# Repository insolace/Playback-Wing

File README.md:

# Playback-Wing
Concept by Survivor Sound (http://www.survivorsound.com/)

Proof of concept prototype developed by Eric Bateman in 2018

<br>
MIDI DEMO VIDEO (with cat at the end)

<br>
LCD DEMO VIDEO

Playback Wing is a portable MIDI powered lighting controller with LCD, meant for use with GrandMA lighting consoles.  

Features:
* Super thick (3/16") PCB, takes any abuse you can throw at it
* PCB uses a custom switch footprint that can accomodate either CherryMX or 5500 series switches, with or without LEDs. Create your own layout! 
* USB and hardware DIN MIDI
* Optional LCD

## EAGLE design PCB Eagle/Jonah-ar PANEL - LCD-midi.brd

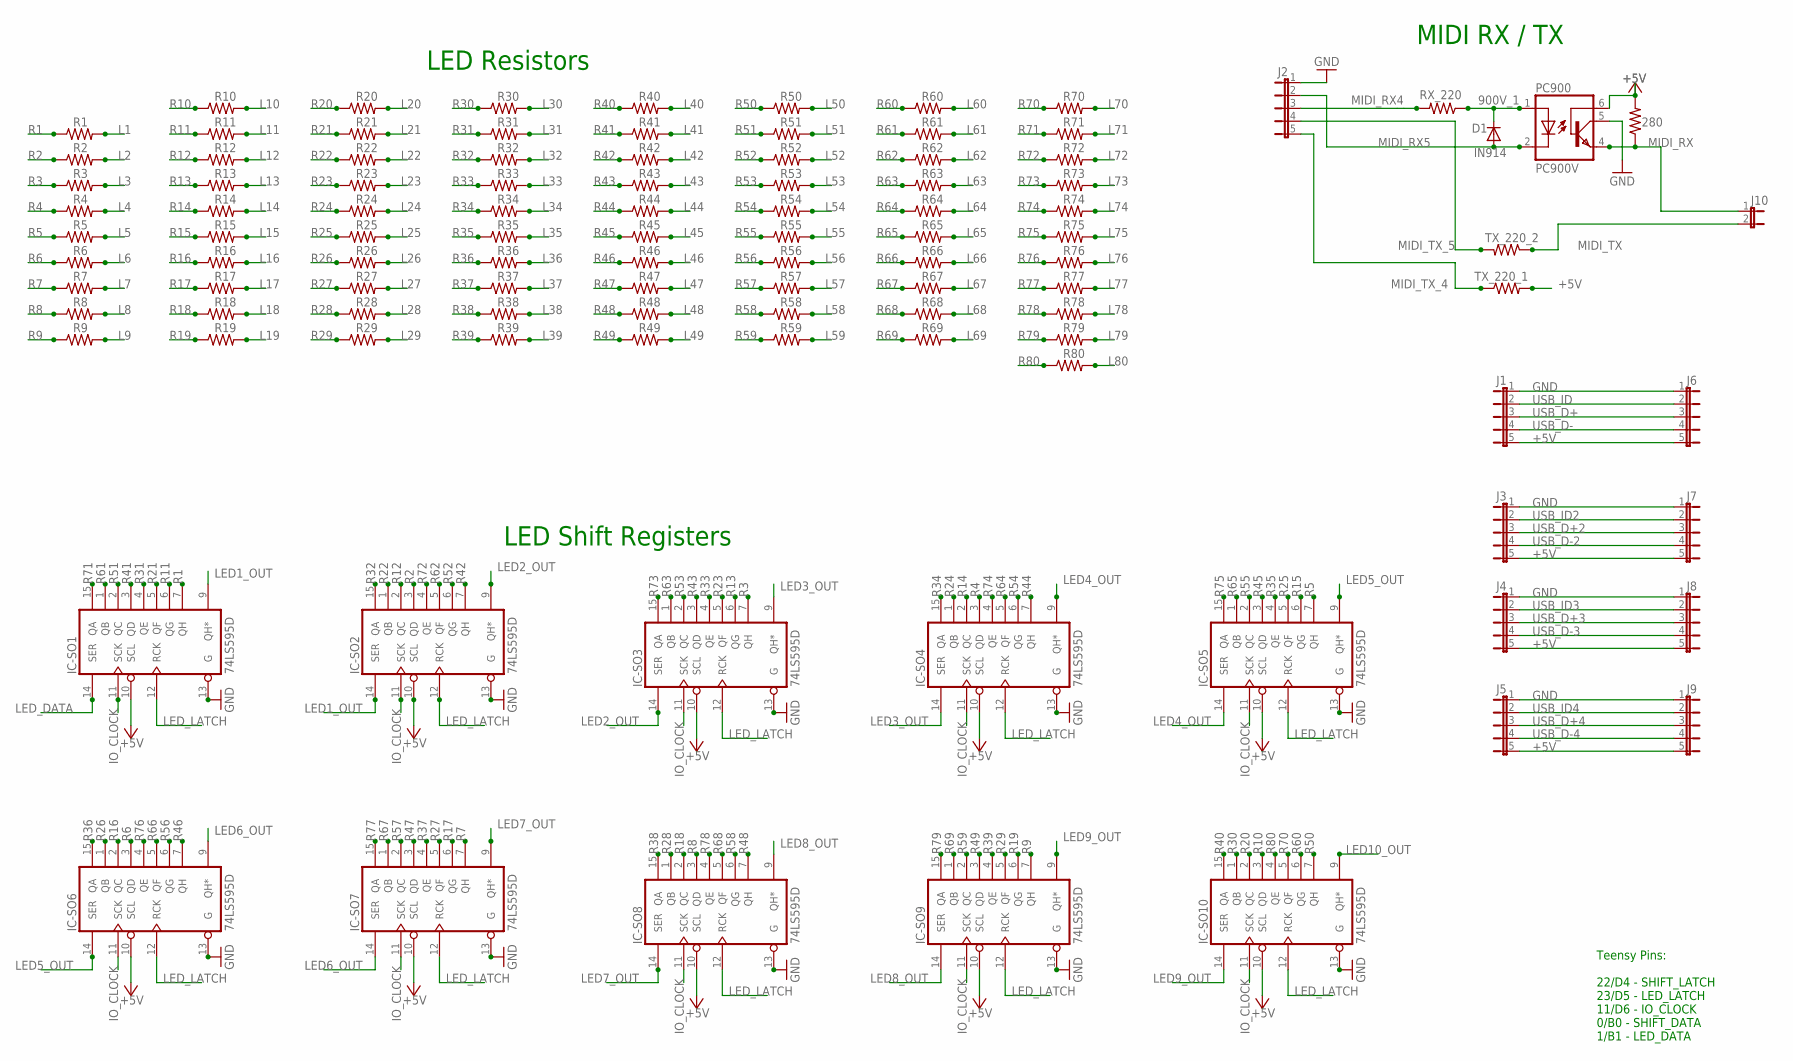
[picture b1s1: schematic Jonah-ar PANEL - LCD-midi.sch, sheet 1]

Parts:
280: 280; 0204/5
D1: IN914; DO34-7
IC-SO1, IC-SO2, IC-SO3, IC-SO4, IC-SO5, IC-SO6, IC-SO7, IC-SO8, IC-SO9, IC-SO10: 74LS595D; SO16
J1, J2, J3, J4, J5, J6, J7, J8, J9: JP5E; JP5
J10: JP1E; JP1
PC900: PC900V; DIL6-SMD
R1, R2, R3, R4, R5, R6, R7, R8, R9, R10, R11, R12, R13, R14, R15, R16, R17, R18, R19, R20, R21, R22, R23, R24, R25, R26, R27, R28, R29, R30, R31, R32, R33, R34, R35, R36, R37, R38, R39, R40, R41, R42, R43, R44, R45, R46, R47, R48, R49, R50, R51, R52, R53, R54, R55, R56, R57, R58, R59, R60, R61, R62, R63, R64, R65, R66, R67, R68, R69, R70, R71, R72, R73, R74, R75, R76, R77, R78, R79, R80: R-US_0204/5; 0204/5
RX_220: 220; 0204/5
TX_220_1, TX_220_2: 220; 0204/5

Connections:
900V_1: D1.C, PC900.1 (A), RX_220.1
+5V: 280.2, IC-SO1.10 (SCL), IC-SO1.16 (+5V), IC-SO2.10 (SCL), IC-SO2.16 (+5V), IC-SO3.10 (SCL), IC-SO3.16 (+5V), IC-SO4.10 (SCL), IC-SO4.16 (+5V), IC-SO5.10 (SCL), IC-SO5.16 (+5V), IC-SO6.10 (SCL), IC-SO6.16 (+5V), IC-SO7.10 (SCL), IC-SO7.16 (+5V), IC-SO8.10 (SCL), IC-SO8.16 (+5V), IC-SO9.10 (SCL), IC-SO9.16 (+5V), IC-SO10.10 (SCL), IC-SO10.16 (+5V), J1.5, J3.5, J4.5, J5.5, J6.5, J7.5, J8.5, J9.5, PC900.6 (BAS), TX_220_1.2; also elsewhere on the board
GND: IC-SO1.8 (GND), IC-SO1.13 (G), IC-SO2.8 (GND), IC-SO2.13 (G), IC-SO3.8 (GND), IC-SO3.13 (G), IC-SO4.8 (GND), IC-SO4.13 (G), IC-SO5.8 (GND), IC-SO5.13 (G), IC-SO6.8 (GND), IC-SO6.13 (G), IC-SO7.8 (GND), IC-SO7.13 (G), IC-SO8.8 (GND), IC-SO8.13 (G), IC-SO9.8 (GND), IC-SO9.13 (G), IC-SO10.8 (GND), IC-SO10.13 (G), J1.1, J2.1, J3.1, J4.1, J5.1, J6.1, J7.1, J8.1, J9.1, PC900.5 (COL); also elsewhere on the board
IO_CLOCK: IC-SO1.11 (SCK), IC-SO2.11 (SCK), IC-SO3.11 (SCK), IC-SO4.11 (SCK), IC-SO5.11 (SCK), IC-SO6.11 (SCK), IC-SO7.11 (SCK), IC-SO8.11 (SCK), IC-SO9.11 (SCK), IC-SO10.11 (SCK); also elsewhere on the board
L1: R1.2; also elsewhere on the board
L2: R2.2; also elsewhere on the board
L3: R3.2; also elsewhere on the board
L4: R4.2; also elsewhere on the board
L5: R5.2; also elsewhere on the board
L6: R6.2; also elsewhere on the board
L7: R7.2; also elsewhere on the board
L8: R8.2; also elsewhere on the board
L9: R9.2; also elsewhere on the board
L10: R10.2; also elsewhere on the board
L11: R11.2; also elsewhere on the board
L12: R12.2; also elsewhere on the board
L13: R13.2; also elsewhere on the board
L14: R14.2; also elsewhere on the board
L15: R15.2; also elsewhere on the board
L16: R16.2; also elsewhere on the board
L17: R17.2; also elsewhere on the board
L18: R18.2; also elsewhere on the board
L19: R19.2; also elsewhere on the board
L20: R20.2; also elsewhere on the board
L21: R21.2; also elsewhere on the board
L22: R22.2; also elsewhere on the board
L23: R23.2; also elsewhere on the board
L24: R24.2; also elsewhere on the board
L25: R25.2; also elsewhere on the board
L26: R26.2; also elsewhere on the board
L27: R27.2; also elsewhere on the board
L28: R28.2; also elsewhere on the board
L29: R29.2; also elsewhere on the board
L30: R30.2; also elsewhere on the board
L31: R31.2; also elsewhere on the board
L32: R32.2; also elsewhere on the board
L33: R33.2; also elsewhere on the board
L34: R34.2; also elsewhere on the board
L35: R35.2; also elsewhere on the board
L36: R36.2; also elsewhere on the board
L37: R37.2; also elsewhere on the board
L38: R38.2; also elsewhere on the board
L39: R39.2; also elsewhere on the board
L40: R40.2; also elsewhere on the board
L41: R41.2; also elsewhere on the board
L42: R42.2; also elsewhere on the board
L43: R43.2; also elsewhere on the board
L44: R44.2; also elsewhere on the board
L45: R45.2; also elsewhere on the board
L46: R46.2; also elsewhere on the board
L47: R47.2; also elsewhere on the board
L48: R48.2; also elsewhere on the board
L49: R49.2; also elsewhere on the board
L50: R50.2; also elsewhere on the board
L51: R51.2; also elsewhere on the board
L52: R52.2; also elsewhere on the board
L53: R53.2; also elsewhere on the board
L54: R54.2; also elsewhere on the board
L55: R55.2; also elsewhere on the board
L56: R56.2; also elsewhere on the board
L57: R57.2; also elsewhere on the board
L58: R58.2; also elsewhere on the board
L59: R59.2; also elsewhere on the board
L60: R60.2; also elsewhere on the board
L61: R61.2; also elsewhere on the board
L62: R62.2; also elsewhere on the board
L63: R63.2; also elsewhere on the board
L64: R64.2; also elsewhere on the board
L65: R65.2; also elsewhere on the board
L66: R66.2; also elsewhere on the board
L67: R67.2; also elsewhere on the board
L68: R68.2; also elsewhere on the board
L69: R69.2; also elsewhere on the board
L70: R70.2; also elsewhere on the board
L71: R71.2; also elsewhere on the board
L72: R72.2; also elsewhere on the board
L73: R73.2; also elsewhere on the board
L74: R74.2; also elsewhere on the board
L75: R75.2; also elsewhere on the board
L76: R76.2; also elsewhere on the board
L77: R77.2; also elsewhere on the board
L78: R78.2; also elsewhere on the board
L79: R79.2; also elsewhere on the board
L80: R80.2; also elsewhere on the board
LED1_OUT: IC-SO1.9 (QH*), IC-SO2.14 (SER)
LED2_OUT: IC-SO2.9 (QH*), IC-SO3.14 (SER)
LED3_OUT: IC-SO3.9 (QH*), IC-SO4.14 (SER)
LED4_OUT: IC-SO4.9 (QH*), IC-SO5.14 (SER)
LED5_OUT: IC-SO5.9 (QH*), IC-SO6.14 (SER)
LED6_OUT: IC-SO6.9 (QH*), IC-SO7.14 (SER)
LED7_OUT: IC-SO7.9 (QH*), IC-SO8.14 (SER)
LED8_OUT: IC-SO8.9 (QH*), IC-SO9.14 (SER)
LED9_OUT: IC-SO9.9 (QH*), IC-SO10.14 (SER)
LED10_OUT: IC-SO10.9 (QH*)
LED_DATA: IC-SO1.14 (SER)
LED_LATCH: IC-SO1.12 (RCK), IC-SO2.12 (RCK), IC-SO3.12 (RCK), IC-SO4.12 (RCK), IC-SO5.12 (RCK), IC-SO6.12 (RCK), IC-SO7.12 (RCK), IC-SO8.12 (RCK), IC-SO9.12 (RCK), IC-SO10.12 (RCK)
MIDI_RX: 280.1, J10.1, PC900.4 (EMI)
MIDI_RX4: J2.3, RX_220.2
MIDI_RX5: D1.A, J2.2, PC900.2 (C)
MIDI_TX: J10.2, TX_220_2.1
MIDI_TX_4: J2.5, TX_220_1.1
MIDI_TX_5: J2.4, TX_220_2.2
R1: IC-SO1.7 (QH), R1.1
R2: IC-SO2.3 (QD), R2.1
R3: IC-SO3.7 (QH), R3.1
R4: IC-SO4.3 (QD), R4.1
R5: IC-SO5.7 (QH), R5.1
R6: IC-SO6.3 (QD), R6.1
R7: IC-SO7.7 (QH), R7.1
R8: IC-SO8.3 (QD), R8.1
R9: IC-SO9.7 (QH), R9.1
R10: IC-SO10.3 (QD), R10.1
R11: IC-SO1.6 (QG), R11.1
R12: IC-SO2.2 (QC), R12.1
R13: IC-SO3.6 (QG), R13.1
R14: IC-SO4.2 (QC), R14.1
R15: IC-SO5.6 (QG), R15.1
R16: IC-SO6.2 (QC), R16.1
R17: IC-SO7.6 (QG), R17.1
R18: IC-SO8.2 (QC), R18.1
R19: IC-SO9.6 (QG), R19.1
R20: IC-SO10.2 (QC), R20.1
R21: IC-SO1.5 (QF), R21.1
R22: IC-SO2.1 (QB), R22.1
R23: IC-SO3.5 (QF), R23.1
R24: IC-SO4.1 (QB), R24.1
R25: IC-SO5.5 (QF), R25.1
R26: IC-SO6.1 (QB), R26.1
R27: IC-SO7.5 (QF), R27.1
R28: IC-SO8.1 (QB), R28.1
R29: IC-SO9.5 (QF), R29.1
R30: IC-SO10.1 (QB), R30.1
R31: IC-SO1.4 (QE), R31.1
R32: IC-SO2.15 (QA), R32.1
R33: IC-SO3.4 (QE), R33.1
R34: IC-SO4.15 (QA), R34.1
R35: IC-SO5.4 (QE), R35.1
R36: IC-SO6.15 (QA), R36.1
R37: IC-SO7.4 (QE), R37.1
R38: IC-SO8.15 (QA), R38.1
R39: IC-SO9.4 (QE), R39.1
R40: IC-SO10.15 (QA), R40.1
R41: IC-SO1.3 (QD), R41.1
R42: IC-SO2.7 (QH), R42.1
R43: IC-SO3.3 (QD), R43.1
R44: IC-SO4.7 (QH), R44.1
R45: IC-SO5.3 (QD), R45.1
R46: IC-SO6.7 (QH), R46.1
R47: IC-SO7.3 (QD), R47.1
R48: IC-SO8.7 (QH), R48.1
R49: IC-SO9.3 (QD), R49.1
R50: IC-SO10.7 (QH), R50.1
R51: IC-SO1.2 (QC), R51.1
R52: IC-SO2.6 (QG), R52.1
R53: IC-SO3.2 (QC), R53.1
R54: IC-SO4.6 (QG), R54.1
R55: IC-SO5.2 (QC), R55.1
R56: IC-SO6.6 (QG), R56.1
R57: IC-SO7.2 (QC), R57.1
R58: IC-SO8.6 (QG), R58.1
R59: IC-SO9.2 (QC), R59.1
R60: IC-SO10.6 (QG), R60.1
R61: IC-SO1.1 (QB), R61.1
R62: IC-SO2.5 (QF), R62.1
R63: IC-SO3.1 (QB), R63.1
R64: IC-SO4.5 (QF), R64.1
R65: IC-SO5.1 (QB), R65.1
R66: IC-SO6.5 (QF), R66.1
R67: IC-SO7.1 (QB), R67.1
R68: IC-SO8.5 (QF), R68.1
R69: IC-SO9.1 (QB), R69.1
R70: IC-SO10.5 (QF), R70.1
R71: IC-SO1.15 (QA), R71.1
R72: IC-SO2.4 (QE), R72.1
R73: IC-SO3.15 (QA), R73.1
R74: IC-SO4.4 (QE), R74.1
R75: IC-SO5.15 (QA), R75.1
R76: IC-SO6.4 (QE), R76.1
R77: IC-SO7.15 (QA), R77.1
R78: IC-SO8.4 (QE), R78.1
R79: IC-SO9.15 (QA), R79.1
R80: IC-SO10.4 (QE), R80.1
USB_D+: J1.3, J6.3
USB_D+2: J3.3, J7.3
USB_D+3: J4.3, J8.3
USB_D+4: J5.3, J9.3
USB_D-: J1.4, J6.4
USB_D-2: J3.4, J7.4
USB_D-3: J4.4, J8.4
USB_D-4: J5.4, J9.4
USB_ID: J1.2, J6.2
USB_ID2: J3.2, J7.2
USB_ID3: J4.2, J8.2
USB_ID4: J5.2, J9.2

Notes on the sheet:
Teensy Pins: 22/D4 - SHIFT_LATCH 23/D5 - LED_LATCH 11/D6 - IO_CLOCK 0/B0 - SHIFT_DATA 1/B1 - LED_DATA
MIDI RX / TX
LED Resistors
LED Shift Registers

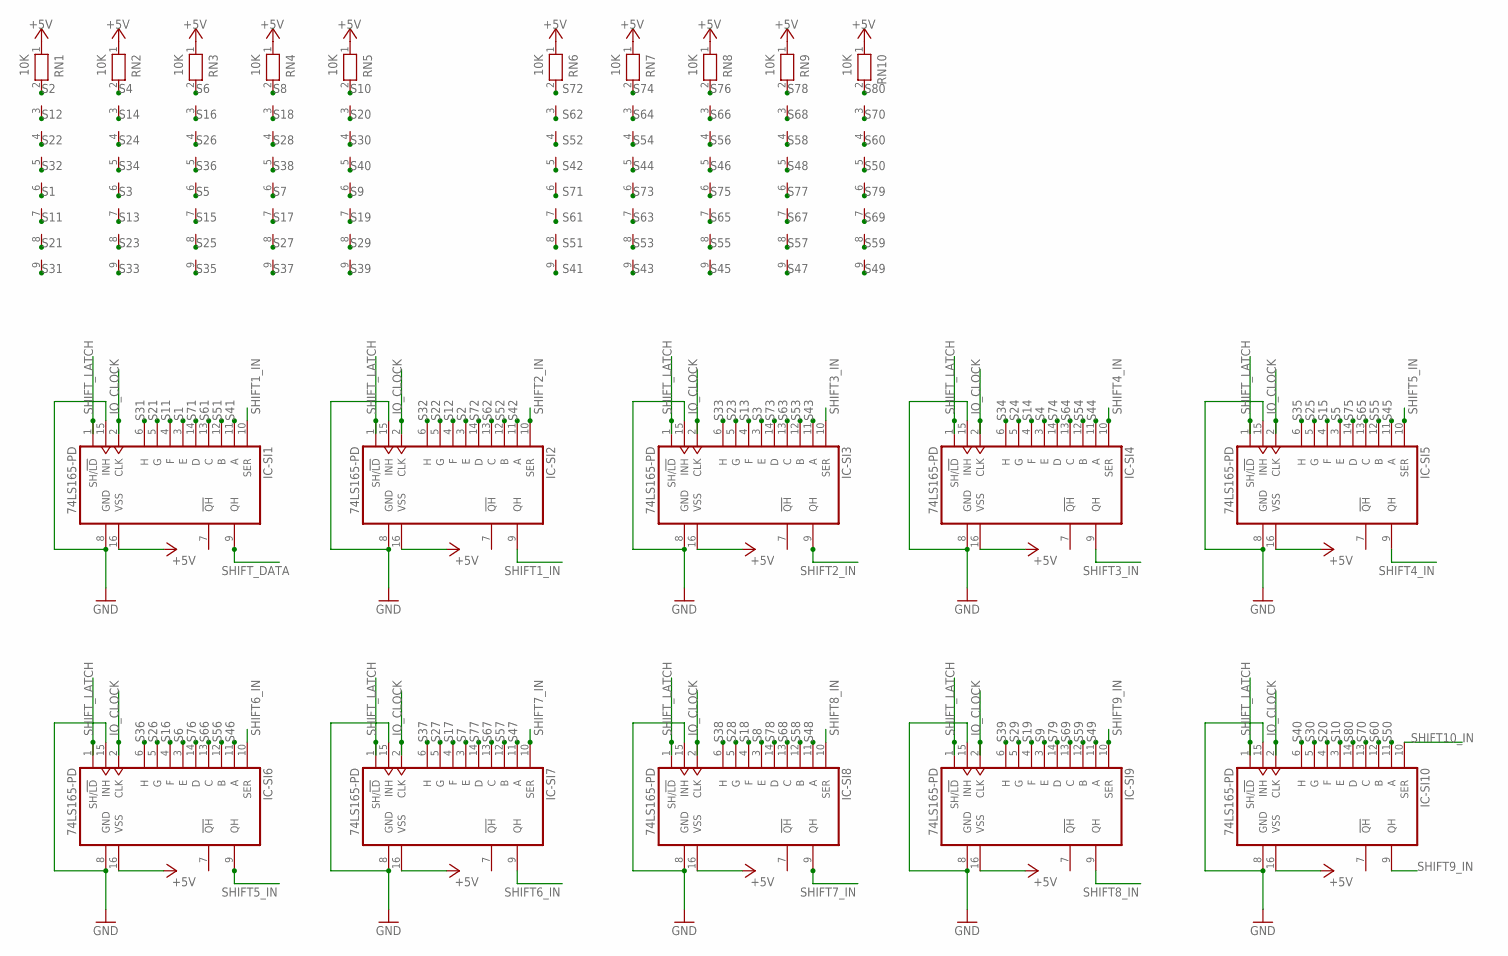
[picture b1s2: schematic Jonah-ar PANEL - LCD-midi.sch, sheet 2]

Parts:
IC-SI1, IC-SI2, IC-SI3, IC-SI4, IC-SI5, IC-SI6, IC-SI7, IC-SI8, IC-SI9, IC-SI10: 74LS165-PD; SO16
RN1, RN2, RN3, RN4, RN5, RN6, RN7, RN8, RN9, RN10: 10K; RN-9

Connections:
+5V: IC-SI1.16 (VSS), IC-SI2.16 (VSS), IC-SI3.16 (VSS), IC-SI4.16 (VSS), IC-SI5.16 (VSS), IC-SI6.16 (VSS), IC-SI7.16 (VSS), IC-SI8.16 (VSS), IC-SI9.16 (VSS), IC-SI10.16 (VSS), RN1.1, RN2.1, RN3.1, RN4.1, RN5.1, RN6.1, RN7.1, RN8.1, RN9.1, RN10.1; also elsewhere on the board
GND: IC-SI1.8 (GND), IC-SI1.15 (INH), IC-SI2.8 (GND), IC-SI2.15 (INH), IC-SI3.8 (GND), IC-SI3.15 (INH), IC-SI4.8 (GND), IC-SI4.15 (INH), IC-SI5.8 (GND), IC-SI5.15 (INH), IC-SI6.8 (GND), IC-SI6.15 (INH), IC-SI7.8 (GND), IC-SI7.15 (INH), IC-SI8.8 (GND), IC-SI8.15 (INH), IC-SI9.8 (GND), IC-SI9.15 (INH), IC-SI10.8 (GND), IC-SI10.15 (INH); also elsewhere on the board
IO_CLOCK: IC-SI1.2 (CLK), IC-SI2.2 (CLK), IC-SI3.2 (CLK), IC-SI4.2 (CLK), IC-SI5.2 (CLK), IC-SI6.2 (CLK), IC-SI7.2 (CLK), IC-SI8.2 (CLK), IC-SI9.2 (CLK), IC-SI10.2 (CLK); also elsewhere on the board
S1: IC-SI1.3 (E), RN1.6; also elsewhere on the board
S2: IC-SI2.3 (E), RN1.2; also elsewhere on the board
S3: IC-SI3.3 (E), RN2.6; also elsewhere on the board
S4: IC-SI4.3 (E), RN2.2; also elsewhere on the board
S5: IC-SI5.3 (E), RN3.6; also elsewhere on the board
S6: IC-SI6.3 (E), RN3.2; also elsewhere on the board
S7: IC-SI7.3 (E), RN4.6; also elsewhere on the board
S8: IC-SI8.3 (E), RN4.2; also elsewhere on the board
S9: IC-SI9.3 (E), RN5.6; also elsewhere on the board
S10: IC-SI10.3 (E), RN5.2; also elsewhere on the board
S11: IC-SI1.4 (F), RN1.7; also elsewhere on the board
S12: IC-SI2.4 (F), RN1.3; also elsewhere on the board
S13: IC-SI3.4 (F), RN2.7; also elsewhere on the board
S14: IC-SI4.4 (F), RN2.3; also elsewhere on the board
S15: IC-SI5.4 (F), RN3.7; also elsewhere on the board
S16: IC-SI6.4 (F), RN3.3; also elsewhere on the board
S17: IC-SI7.4 (F), RN4.7; also elsewhere on the board
S18: IC-SI8.4 (F), RN4.3; also elsewhere on the board
S19: IC-SI9.4 (F), RN5.7; also elsewhere on the board
S20: IC-SI10.4 (F), RN5.3; also elsewhere on the board
S21: IC-SI1.5 (G), RN1.8; also elsewhere on the board
S22: IC-SI2.5 (G), RN1.4; also elsewhere on the board
S23: IC-SI3.5 (G), RN2.8; also elsewhere on the board
S24: IC-SI4.5 (G), RN2.4; also elsewhere on the board
S25: IC-SI5.5 (G), RN3.8; also elsewhere on the board
S26: IC-SI6.5 (G), RN3.4; also elsewhere on the board
S27: IC-SI7.5 (G), RN4.8; also elsewhere on the board
S28: IC-SI8.5 (G), RN4.4; also elsewhere on the board
S29: IC-SI9.5 (G), RN5.8; also elsewhere on the board
S30: IC-SI10.5 (G), RN5.4; also elsewhere on the board
S31: IC-SI1.6 (H), RN1.9; also elsewhere on the board
S32: IC-SI2.6 (H), RN1.5; also elsewhere on the board
S33: IC-SI3.6 (H), RN2.9; also elsewhere on the board
S34: IC-SI4.6 (H), RN2.5; also elsewhere on the board
S35: IC-SI5.6 (H), RN3.9; also elsewhere on the board
S36: IC-SI6.6 (H), RN3.5; also elsewhere on the board
S37: IC-SI7.6 (H), RN4.9; also elsewhere on the board
S38: IC-SI8.6 (H), RN4.5; also elsewhere on the board
S39: IC-SI9.6 (H), RN5.9; also elsewhere on the board
S40: IC-SI10.6 (H), RN5.5; also elsewhere on the board
S41: IC-SI1.11 (A), RN6.9; also elsewhere on the board
S42: IC-SI2.11 (A), RN6.5; also elsewhere on the board
S43: IC-SI3.11 (A), RN7.9; also elsewhere on the board
S44: IC-SI4.11 (A), RN7.5; also elsewhere on the board
S45: IC-SI5.11 (A), RN8.9; also elsewhere on the board
S46: IC-SI6.11 (A), RN8.5; also elsewhere on the board
S47: IC-SI7.11 (A), RN9.9; also elsewhere on the board
S48: IC-SI8.11 (A), RN9.5; also elsewhere on the board
S49: IC-SI9.11 (A), RN10.9; also elsewhere on the board
S50: IC-SI10.11 (A), RN10.5; also elsewhere on the board
S51: IC-SI1.12 (B), RN6.8; also elsewhere on the board
S52: IC-SI2.12 (B), RN6.4; also elsewhere on the board
S53: IC-SI3.12 (B), RN7.8; also elsewhere on the board
S54: IC-SI4.12 (B), RN7.4; also elsewhere on the board
S55: IC-SI5.12 (B), RN8.8; also elsewhere on the board
S56: IC-SI6.12 (B), RN8.4; also elsewhere on the board
S57: IC-SI7.12 (B), RN9.8; also elsewhere on the board
S58: IC-SI8.12 (B), RN9.4; also elsewhere on the board
S59: IC-SI9.12 (B), RN10.8; also elsewhere on the board
S60: IC-SI10.12 (B), RN10.4; also elsewhere on the board
S61: IC-SI1.13 (C), RN6.7; also elsewhere on the board
S62: IC-SI2.13 (C), RN6.3; also elsewhere on the board
S63: IC-SI3.13 (C), RN7.7; also elsewhere on the board
S64: IC-SI4.13 (C), RN7.3; also elsewhere on the board
S65: IC-SI5.13 (C), RN8.7; also elsewhere on the board
S66: IC-SI6.13 (C), RN8.3; also elsewhere on the board
S67: IC-SI7.13 (C), RN9.7; also elsewhere on the board
S68: IC-SI8.13 (C), RN9.3; also elsewhere on the board
S69: IC-SI9.13 (C), RN10.7; also elsewhere on the board
S70: IC-SI10.13 (C), RN10.3; also elsewhere on the board
S71: IC-SI1.14 (D), RN6.6; also elsewhere on the board
S72: IC-SI2.14 (D), RN6.2; also elsewhere on the board
S73: IC-SI3.14 (D), RN7.6; also elsewhere on the board
S74: IC-SI4.14 (D), RN7.2; also elsewhere on the board
S75: IC-SI5.14 (D), RN8.6; also elsewhere on the board
S76: IC-SI6.14 (D), RN8.2; also elsewhere on the board
S77: IC-SI7.14 (D), RN9.6; also elsewhere on the board
S78: IC-SI8.14 (D), RN9.2; also elsewhere on the board
S79: IC-SI9.14 (D), RN10.6; also elsewhere on the board
S80: IC-SI10.14 (D), RN10.2; also elsewhere on the board
SHIFT1_IN: IC-SI1.10 (SER), IC-SI2.9 (QH)
SHIFT2_IN: IC-SI2.10 (SER), IC-SI3.9 (QH)
SHIFT3_IN: IC-SI3.10 (SER), IC-SI4.9 (QH)
SHIFT4_IN: IC-SI4.10 (SER), IC-SI5.9 (QH)
SHIFT5_IN: IC-SI5.10 (SER), IC-SI6.9 (QH)
SHIFT6_IN: IC-SI6.10 (SER), IC-SI7.9 (QH)
SHIFT7_IN: IC-SI7.10 (SER), IC-SI8.9 (QH)
SHIFT8_IN: IC-SI8.10 (SER), IC-SI9.9 (QH)
SHIFT9_IN: IC-SI9.10 (SER), IC-SI10.9 (QH)
SHIFT10_IN: IC-SI10.10 (SER)
SHIFT_DATA: IC-SI1.9 (QH)
SHIFT_LATCH: IC-SI1.1 (SH/!LD), IC-SI2.1 (SH/!LD), IC-SI3.1 (SH/!LD), IC-SI4.1 (SH/!LD), IC-SI5.1 (SH/!LD), IC-SI6.1 (SH/!LD), IC-SI7.1 (SH/!LD), IC-SI8.1 (SH/!LD), IC-SI9.1 (SH/!LD), IC-SI10.1 (SH/!LD)

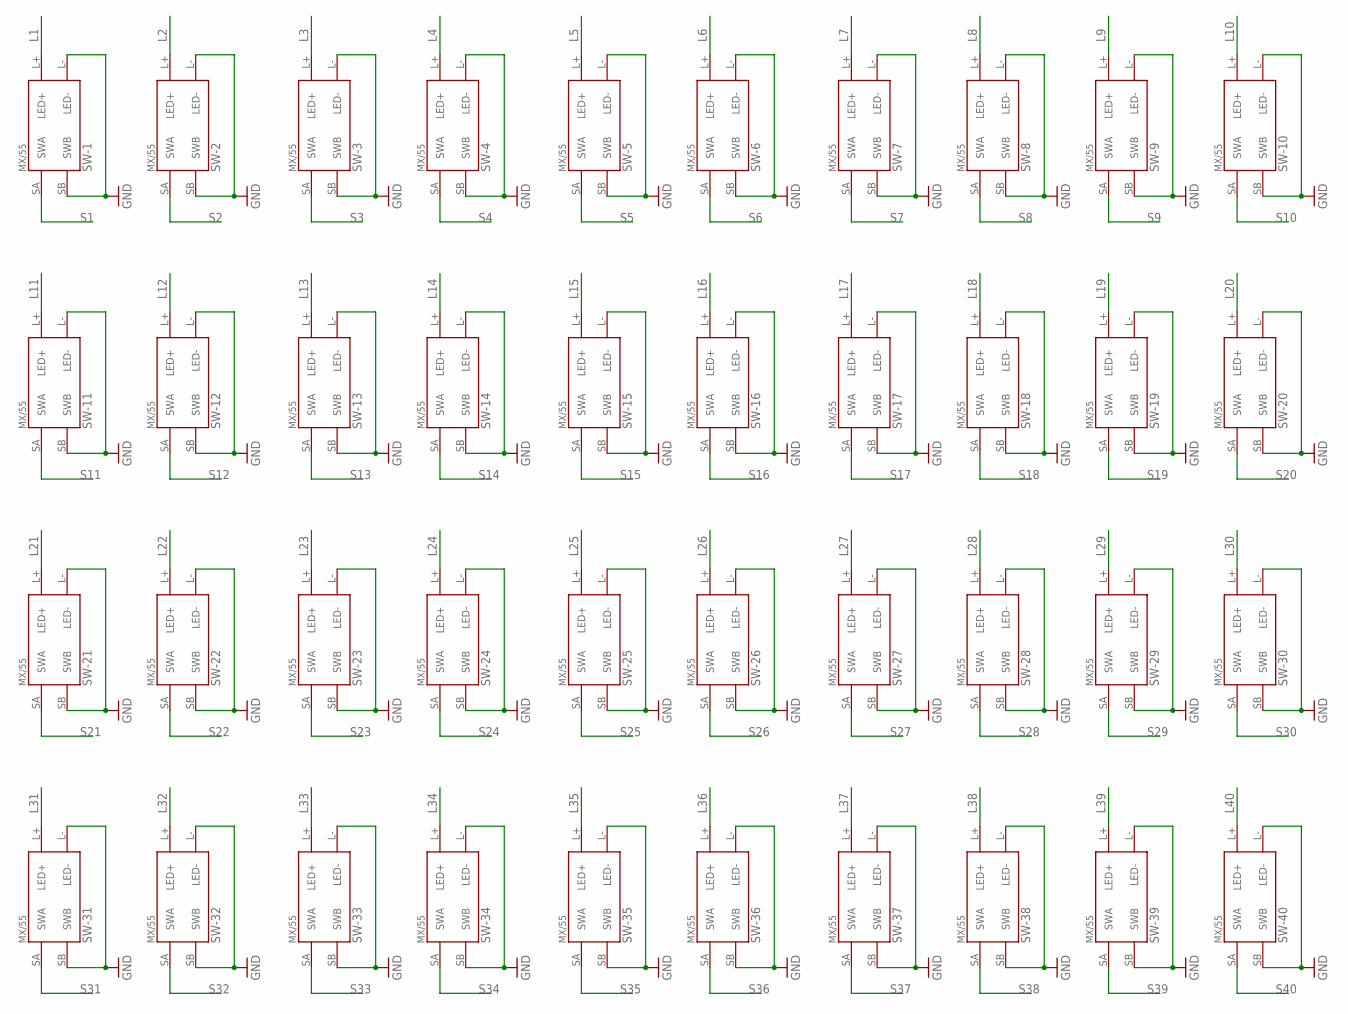
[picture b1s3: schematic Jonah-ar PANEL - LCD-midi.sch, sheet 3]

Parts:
SW-1, SW-2, SW-3, SW-4, SW-5, SW-6, SW-7, SW-8, SW-9, SW-10, SW-11, SW-12, SW-13, SW-14, SW-15, SW-16, SW-17, SW-18, SW-19, SW-20, SW-21, SW-22, SW-23, SW-24, SW-25, SW-26, SW-27, SW-28, SW-29, SW-30, SW-31, SW-32, SW-33, SW-34, SW-35, SW-36, SW-37, SW-38, SW-39, SW-40: CHERRY-MX-LED

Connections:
GND: SW-1.L- (LED-), SW-1.SB (SWB), SW-2.L- (LED-), SW-2.SB (SWB), SW-3.L- (LED-), SW-3.SB (SWB), SW-4.L- (LED-), SW-4.SB (SWB), SW-5.L- (LED-), SW-5.SB (SWB), SW-6.L- (LED-), SW-6.SB (SWB), SW-7.L- (LED-), SW-7.SB (SWB), SW-8.L- (LED-), SW-8.SB (SWB), SW-9.L- (LED-), SW-9.SB (SWB), SW-10.L- (LED-), SW-10.SB (SWB), SW-11.L- (LED-), SW-11.SB (SWB), SW-12.L- (LED-), SW-12.SB (SWB), SW-13.L- (LED-), SW-13.SB (SWB), SW-14.L- (LED-), SW-14.SB (SWB), SW-15.L- (LED-), SW-15.SB (SWB), SW-16.L- (LED-), SW-16.SB (SWB), SW-17.L- (LED-), SW-17.SB (SWB), SW-18.L- (LED-), SW-18.SB (SWB), SW-19.L- (LED-), SW-19.SB (SWB), SW-20.L- (LED-), SW-20.SB (SWB), SW-21.L- (LED-), SW-21.SB (SWB), SW-22.L- (LED-), SW-22.SB (SWB), SW-23.L- (LED-), SW-23.SB (SWB), SW-24.L- (LED-), SW-24.SB (SWB), SW-25.L- (LED-), SW-25.SB (SWB), SW-26.L- (LED-), SW-26.SB (SWB), SW-27.L- (LED-), SW-27.SB (SWB), SW-28.L- (LED-), SW-28.SB (SWB), SW-29.L- (LED-), SW-29.SB (SWB), SW-30.L- (LED-), SW-30.SB (SWB), SW-31.L- (LED-), SW-31.SB (SWB), SW-32.L- (LED-), SW-32.SB (SWB), SW-33.L- (LED-), SW-33.SB (SWB), SW-34.L- (LED-), SW-34.SB (SWB), SW-35.L- (LED-), SW-35.SB (SWB), SW-36.L- (LED-), SW-36.SB (SWB), SW-37.L- (LED-), SW-37.SB (SWB), SW-38.L- (LED-), SW-38.SB (SWB), SW-39.L- (LED-), SW-39.SB (SWB), SW-40.L- (LED-), SW-40.SB (SWB); also elsewhere on the board
L1: SW-1.L+ (LED+); also elsewhere on the board
L2: SW-2.L+ (LED+); also elsewhere on the board
L3: SW-3.L+ (LED+); also elsewhere on the board
L4: SW-4.L+ (LED+); also elsewhere on the board
L5: SW-5.L+ (LED+); also elsewhere on the board
L6: SW-6.L+ (LED+); also elsewhere on the board
L7: SW-7.L+ (LED+); also elsewhere on the board
L8: SW-8.L+ (LED+); also elsewhere on the board
L9: SW-9.L+ (LED+); also elsewhere on the board
L10: SW-10.L+ (LED+); also elsewhere on the board
L11: SW-11.L+ (LED+); also elsewhere on the board
L12: SW-12.L+ (LED+); also elsewhere on the board
L13: SW-13.L+ (LED+); also elsewhere on the board
L14: SW-14.L+ (LED+); also elsewhere on the board
L15: SW-15.L+ (LED+); also elsewhere on the board
L16: SW-16.L+ (LED+); also elsewhere on the board
L17: SW-17.L+ (LED+); also elsewhere on the board
L18: SW-18.L+ (LED+); also elsewhere on the board
L19: SW-19.L+ (LED+); also elsewhere on the board
L20: SW-20.L+ (LED+); also elsewhere on the board
L21: SW-21.L+ (LED+); also elsewhere on the board
L22: SW-22.L+ (LED+); also elsewhere on the board
L23: SW-23.L+ (LED+); also elsewhere on the board
L24: SW-24.L+ (LED+); also elsewhere on the board
L25: SW-25.L+ (LED+); also elsewhere on the board
L26: SW-26.L+ (LED+); also elsewhere on the board
L27: SW-27.L+ (LED+); also elsewhere on the board
L28: SW-28.L+ (LED+); also elsewhere on the board
L29: SW-29.L+ (LED+); also elsewhere on the board
L30: SW-30.L+ (LED+); also elsewhere on the board
L31: SW-31.L+ (LED+); also elsewhere on the board
L32: SW-32.L+ (LED+); also elsewhere on the board
L33: SW-33.L+ (LED+); also elsewhere on the board
L34: SW-34.L+ (LED+); also elsewhere on the board
L35: SW-35.L+ (LED+); also elsewhere on the board
L36: SW-36.L+ (LED+); also elsewhere on the board
L37: SW-37.L+ (LED+); also elsewhere on the board
L38: SW-38.L+ (LED+); also elsewhere on the board
L39: SW-39.L+ (LED+); also elsewhere on the board
L40: SW-40.L+ (LED+); also elsewhere on the board
S1: SW-1.SA (SWA); also elsewhere on the board
S2: SW-2.SA (SWA); also elsewhere on the board
S3: SW-3.SA (SWA); also elsewhere on the board
S4: SW-4.SA (SWA); also elsewhere on the board
S5: SW-5.SA (SWA); also elsewhere on the board
S6: SW-6.SA (SWA); also elsewhere on the board
S7: SW-7.SA (SWA); also elsewhere on the board
S8: SW-8.SA (SWA); also elsewhere on the board
S9: SW-9.SA (SWA); also elsewhere on the board
S10: SW-10.SA (SWA); also elsewhere on the board
S11: SW-11.SA (SWA); also elsewhere on the board
S12: SW-12.SA (SWA); also elsewhere on the board
S13: SW-13.SA (SWA); also elsewhere on the board
S14: SW-14.SA (SWA); also elsewhere on the board
S15: SW-15.SA (SWA); also elsewhere on the board
S16: SW-16.SA (SWA); also elsewhere on the board
S17: SW-17.SA (SWA); also elsewhere on the board
S18: SW-18.SA (SWA); also elsewhere on the board
S19: SW-19.SA (SWA); also elsewhere on the board
S20: SW-20.SA (SWA); also elsewhere on the board
S21: SW-21.SA (SWA); also elsewhere on the board
S22: SW-22.SA (SWA); also elsewhere on the board
S23: SW-23.SA (SWA); also elsewhere on the board
S24: SW-24.SA (SWA); also elsewhere on the board
S25: SW-25.SA (SWA); also elsewhere on the board
S26: SW-26.SA (SWA); also elsewhere on the board
S27: SW-27.SA (SWA); also elsewhere on the board
S28: SW-28.SA (SWA); also elsewhere on the board
S29: SW-29.SA (SWA); also elsewhere on the board
S30: SW-30.SA (SWA); also elsewhere on the board
S31: SW-31.SA (SWA); also elsewhere on the board
S32: SW-32.SA (SWA); also elsewhere on the board
S33: SW-33.SA (SWA); also elsewhere on the board
S34: SW-34.SA (SWA); also elsewhere on the board
S35: SW-35.SA (SWA); also elsewhere on the board
S36: SW-36.SA (SWA); also elsewhere on the board
S37: SW-37.SA (SWA); also elsewhere on the board
S38: SW-38.SA (SWA); also elsewhere on the board
S39: SW-39.SA (SWA); also elsewhere on the board
S40: SW-40.SA (SWA); also elsewhere on the board

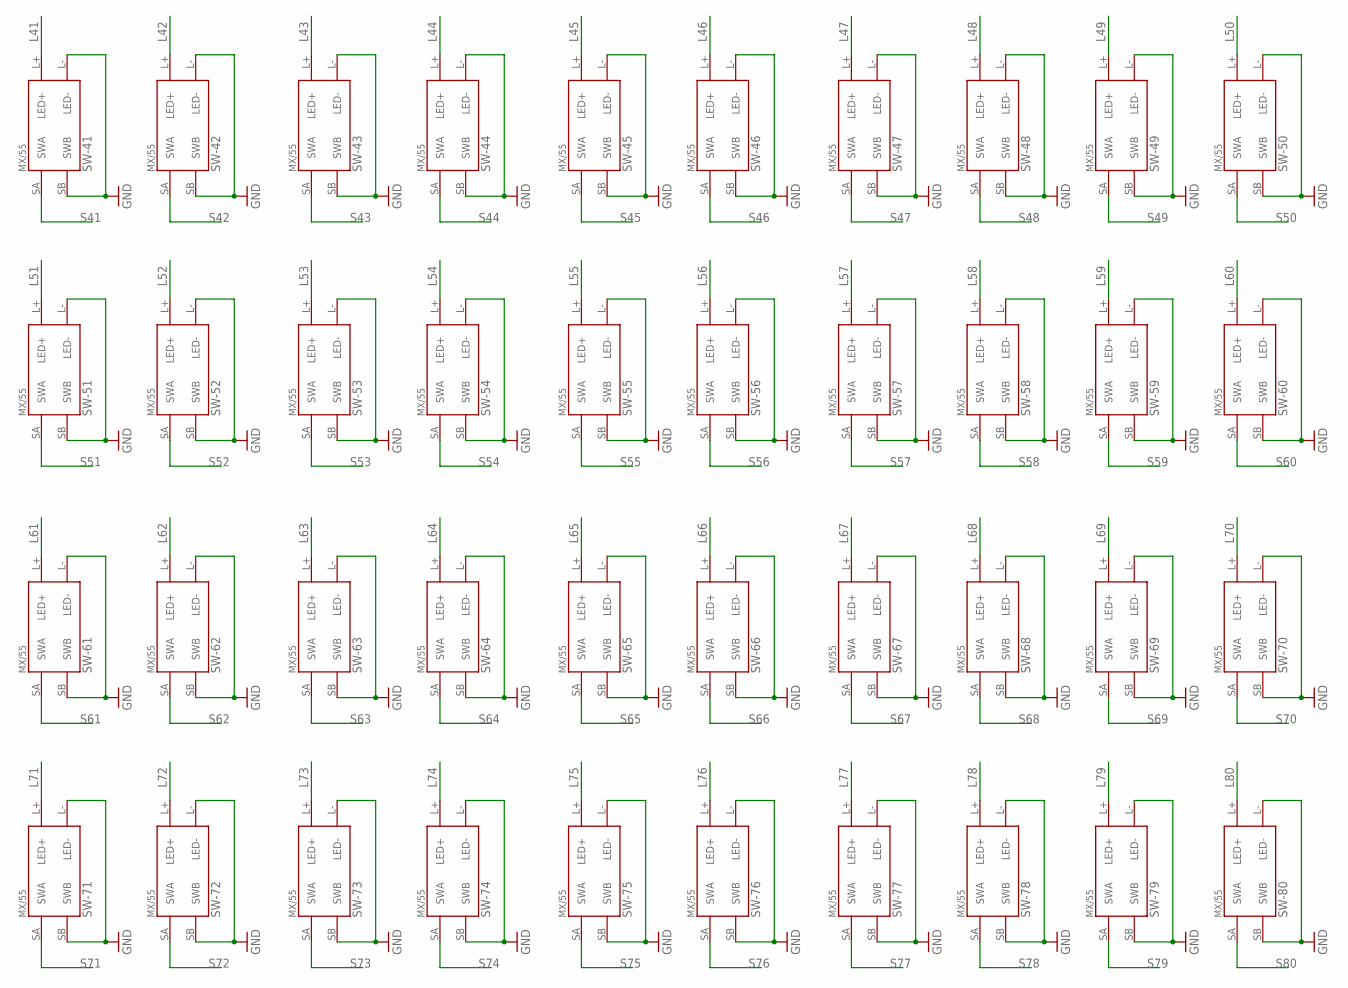
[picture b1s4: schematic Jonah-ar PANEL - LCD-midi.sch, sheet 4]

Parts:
SW-41, SW-42, SW-43, SW-44, SW-45, SW-46, SW-47, SW-48, SW-49, SW-50, SW-51, SW-52, SW-53, SW-54, SW-55, SW-56, SW-57, SW-58, SW-59, SW-60, SW-61, SW-62, SW-63, SW-64, SW-65, SW-66, SW-67, SW-68, SW-69, SW-70, SW-71, SW-72, SW-73, SW-74, SW-75, SW-76, SW-77, SW-78, SW-79, SW-80: CHERRY-MX-LED

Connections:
GND: SW-41.L- (LED-), SW-41.SB (SWB), SW-42.L- (LED-), SW-42.SB (SWB), SW-43.L- (LED-), SW-43.SB (SWB), SW-44.L- (LED-), SW-44.SB (SWB), SW-45.L- (LED-), SW-45.SB (SWB), SW-46.L- (LED-), SW-46.SB (SWB), SW-47.L- (LED-), SW-47.SB (SWB), SW-48.L- (LED-), SW-48.SB (SWB), SW-49.L- (LED-), SW-49.SB (SWB), SW-50.L- (LED-), SW-50.SB (SWB), SW-51.L- (LED-), SW-51.SB (SWB), SW-52.L- (LED-), SW-52.SB (SWB), SW-53.L- (LED-), SW-53.SB (SWB), SW-54.L- (LED-), SW-54.SB (SWB), SW-55.L- (LED-), SW-55.SB (SWB), SW-56.L- (LED-), SW-56.SB (SWB), SW-57.L- (LED-), SW-57.SB (SWB), SW-58.L- (LED-), SW-58.SB (SWB), SW-59.L- (LED-), SW-59.SB (SWB), SW-60.L- (LED-), SW-60.SB (SWB), SW-61.L- (LED-), SW-61.SB (SWB), SW-62.L- (LED-), SW-62.SB (SWB), SW-63.L- (LED-), SW-63.SB (SWB), SW-64.L- (LED-), SW-64.SB (SWB), SW-65.L- (LED-), SW-65.SB (SWB), SW-66.L- (LED-), SW-66.SB (SWB), SW-67.L- (LED-), SW-67.SB (SWB), SW-68.L- (LED-), SW-68.SB (SWB), SW-69.L- (LED-), SW-69.SB (SWB), SW-70.L- (LED-), SW-70.SB (SWB), SW-71.L- (LED-), SW-71.SB (SWB), SW-72.L- (LED-), SW-72.SB (SWB), SW-73.L- (LED-), SW-73.SB (SWB), SW-74.L- (LED-), SW-74.SB (SWB), SW-75.L- (LED-), SW-75.SB (SWB), SW-76.L- (LED-), SW-76.SB (SWB), SW-77.L- (LED-), SW-77.SB (SWB), SW-78.L- (LED-), SW-78.SB (SWB), SW-79.L- (LED-), SW-79.SB (SWB), SW-80.L- (LED-), SW-80.SB (SWB); also elsewhere on the board
L41: SW-41.L+ (LED+); also elsewhere on the board
L42: SW-42.L+ (LED+); also elsewhere on the board
L43: SW-43.L+ (LED+); also elsewhere on the board
L44: SW-44.L+ (LED+); also elsewhere on the board
L45: SW-45.L+ (LED+); also elsewhere on the board
L46: SW-46.L+ (LED+); also elsewhere on the board
L47: SW-47.L+ (LED+); also elsewhere on the board
L48: SW-48.L+ (LED+); also elsewhere on the board
L49: SW-49.L+ (LED+); also elsewhere on the board
L50: SW-50.L+ (LED+); also elsewhere on the board
L51: SW-51.L+ (LED+); also elsewhere on the board
L52: SW-52.L+ (LED+); also elsewhere on the board
L53: SW-53.L+ (LED+); also elsewhere on the board
L54: SW-54.L+ (LED+); also elsewhere on the board
L55: SW-55.L+ (LED+); also elsewhere on the board
L56: SW-56.L+ (LED+); also elsewhere on the board
L57: SW-57.L+ (LED+); also elsewhere on the board
L58: SW-58.L+ (LED+); also elsewhere on the board
L59: SW-59.L+ (LED+); also elsewhere on the board
L60: SW-60.L+ (LED+); also elsewhere on the board
L61: SW-61.L+ (LED+); also elsewhere on the board
L62: SW-62.L+ (LED+); also elsewhere on the board
L63: SW-63.L+ (LED+); also elsewhere on the board
L64: SW-64.L+ (LED+); also elsewhere on the board
L65: SW-65.L+ (LED+); also elsewhere on the board
L66: SW-66.L+ (LED+); also elsewhere on the board
L67: SW-67.L+ (LED+); also elsewhere on the board
L68: SW-68.L+ (LED+); also elsewhere on the board
L69: SW-69.L+ (LED+); also elsewhere on the board
L70: SW-70.L+ (LED+); also elsewhere on the board
L71: SW-71.L+ (LED+); also elsewhere on the board
L72: SW-72.L+ (LED+); also elsewhere on the board
L73: SW-73.L+ (LED+); also elsewhere on the board
L74: SW-74.L+ (LED+); also elsewhere on the board
L75: SW-75.L+ (LED+); also elsewhere on the board
L76: SW-76.L+ (LED+); also elsewhere on the board
L77: SW-77.L+ (LED+); also elsewhere on the board
L78: SW-78.L+ (LED+); also elsewhere on the board
L79: SW-79.L+ (LED+); also elsewhere on the board
L80: SW-80.L+ (LED+); also elsewhere on the board
S41: SW-41.SA (SWA); also elsewhere on the board
S42: SW-42.SA (SWA); also elsewhere on the board
S43: SW-43.SA (SWA); also elsewhere on the board
S44: SW-44.SA (SWA); also elsewhere on the board
S45: SW-45.SA (SWA); also elsewhere on the board
S46: SW-46.SA (SWA); also elsewhere on the board
S47: SW-47.SA (SWA); also elsewhere on the board
S48: SW-48.SA (SWA); also elsewhere on the board
S49: SW-49.SA (SWA); also elsewhere on the board
S50: SW-50.SA (SWA); also elsewhere on the board
S51: SW-51.SA (SWA); also elsewhere on the board
S52: SW-52.SA (SWA); also elsewhere on the board
S53: SW-53.SA (SWA); also elsewhere on the board
S54: SW-54.SA (SWA); also elsewhere on the board
S55: SW-55.SA (SWA); also elsewhere on the board
S56: SW-56.SA (SWA); also elsewhere on the board
S57: SW-57.SA (SWA); also elsewhere on the board
S58: SW-58.SA (SWA); also elsewhere on the board
S59: SW-59.SA (SWA); also elsewhere on the board
S60: SW-60.SA (SWA); also elsewhere on the board
S61: SW-61.SA (SWA); also elsewhere on the board
S62: SW-62.SA (SWA); also elsewhere on the board
S63: SW-63.SA (SWA); also elsewhere on the board
S64: SW-64.SA (SWA); also elsewhere on the board
S65: SW-65.SA (SWA); also elsewhere on the board
S66: SW-66.SA (SWA); also elsewhere on the board
S67: SW-67.SA (SWA); also elsewhere on the board
S68: SW-68.SA (SWA); also elsewhere on the board
S69: SW-69.SA (SWA); also elsewhere on the board
S70: SW-70.SA (SWA); also elsewhere on the board
S71: SW-71.SA (SWA); also elsewhere on the board
S72: SW-72.SA (SWA); also elsewhere on the board
S73: SW-73.SA (SWA); also elsewhere on the board
S74: SW-74.SA (SWA); also elsewhere on the board
S75: SW-75.SA (SWA); also elsewhere on the board
S76: SW-76.SA (SWA); also elsewhere on the board
S77: SW-77.SA (SWA); also elsewhere on the board
S78: SW-78.SA (SWA); also elsewhere on the board
S79: SW-79.SA (SWA); also elsewhere on the board
S80: SW-80.SA (SWA); also elsewhere on the board
